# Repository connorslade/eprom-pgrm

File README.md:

# eprom-pgrm

Reader and programmer for 27 series EPROMs.

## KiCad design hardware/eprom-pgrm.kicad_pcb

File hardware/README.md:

# hardware

[View PCB / Schematic with KiCanvas](https://kicanvas.org/?repo=https%3A%2F%2Fgithub.com%2Fconnorslade%2Feprom-pgrm%2Ftree%2Fmain%2Fhardware)

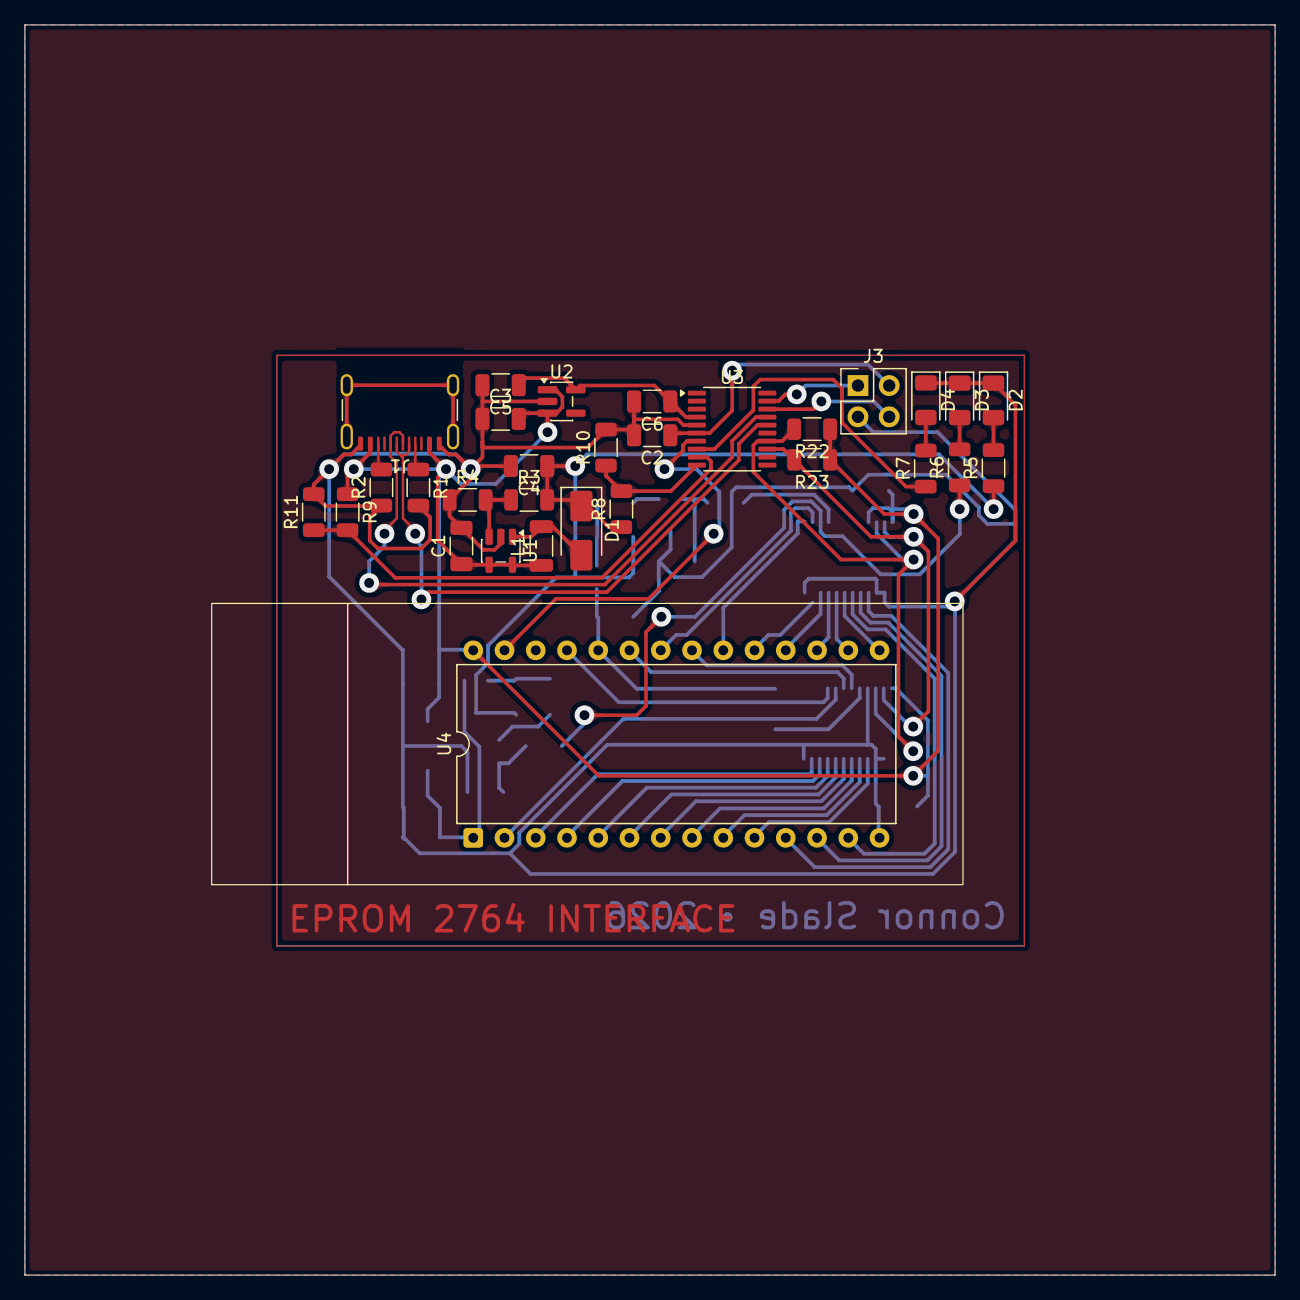
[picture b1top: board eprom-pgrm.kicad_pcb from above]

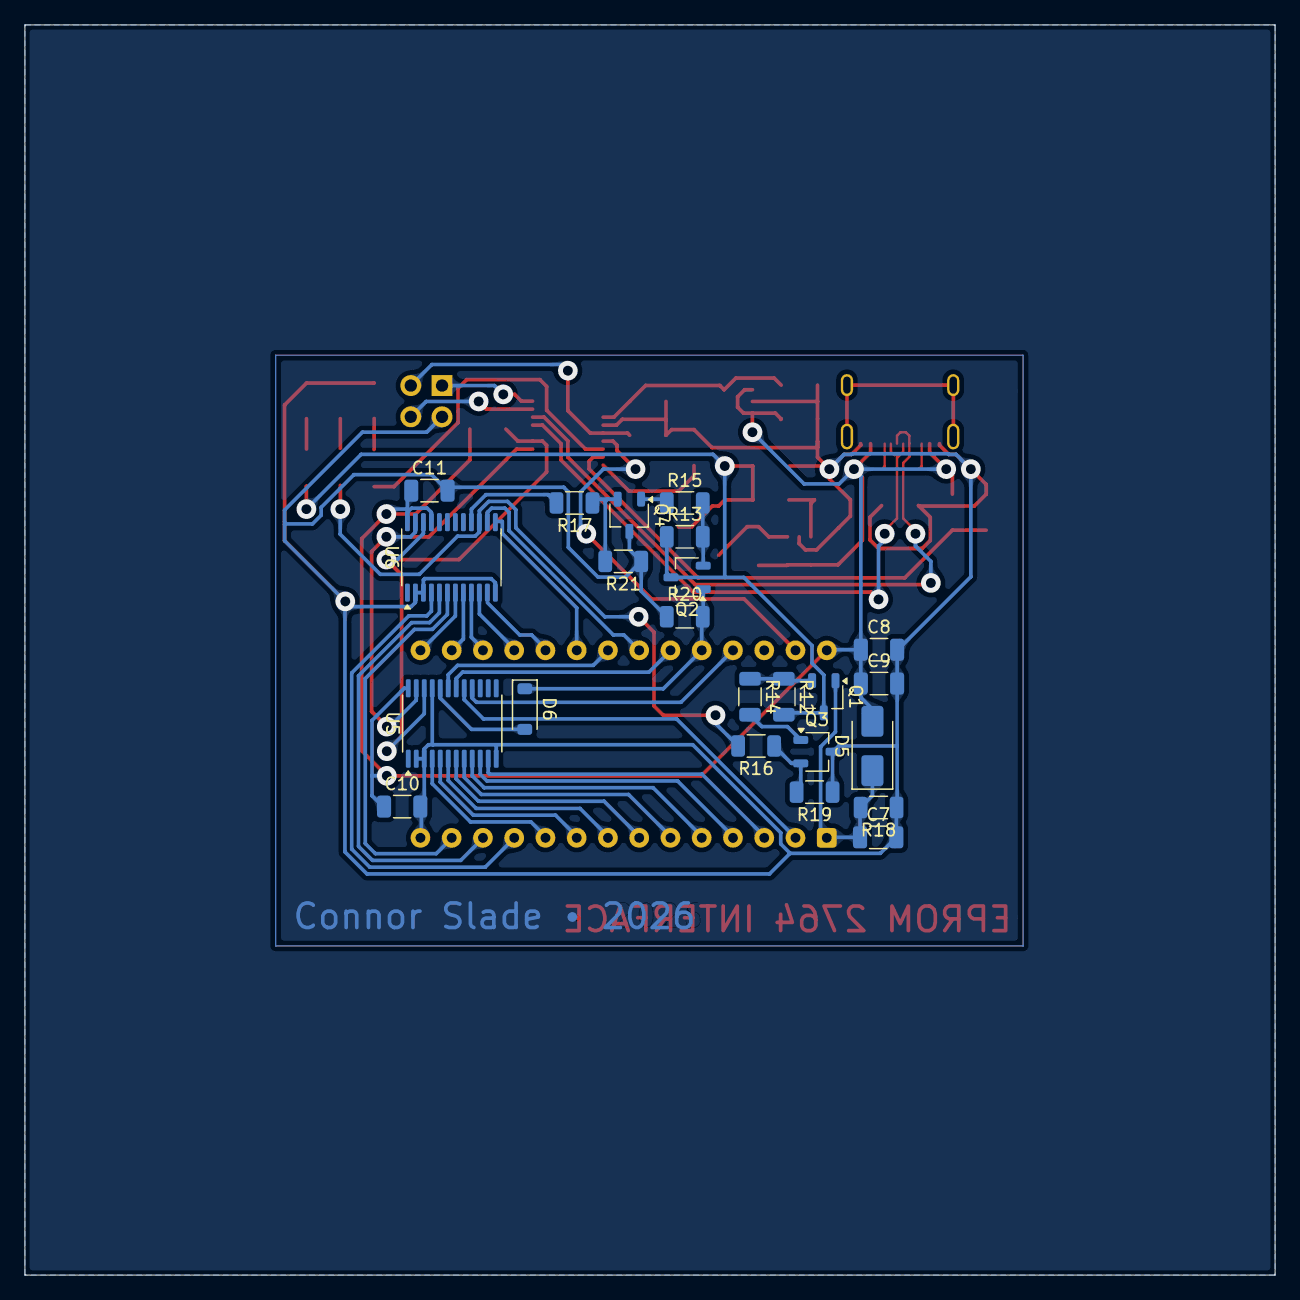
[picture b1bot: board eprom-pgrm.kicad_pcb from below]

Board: 2 copper layers, 101.6 x 101.6 mm, 53 parts (23 on the bottom side), 55 nets.

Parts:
C1, C4: 4.7μF; C_1206_3216Metric
C2: 10nF; C_1206_3216Metric
C3, C6, C7, C9, C10, C11: 100nF; C_1206_3216Metric
C5, C8: 1μF; C_1206_3216Metric
D1, D5: D_SBD; D_SMA
D2, D3, D4: LED; LED_1206_3216Metric
D6: A7; D_SOD-123
J1: USB_C_USB2.0_16P; GCT_USB4105-03-A
J3: Conn_02x02; PinHeader_2x02_P2.54mm_Vertical
L1: 10μH; L_1206_3216Metric
Q1, Q2: PNP; TSOT-23
Q3, Q4: NPN; TSOT-23
R1, R2: 5.1kΩ; R_1206_3216Metric
R3: 91kΩ; R_1206_3216Metric
R4, R12, R13, R18, R20: 10kΩ; R_1206_3216Metric
R5, R14, R15: 2kΩ; R_1206_3216Metric
R6, R7: 330Ω; R_1206_3216Metric
R8: 100kΩ; R_1206_3216Metric
R9: 39kΩ; R_1206_3216Metric
R10: 20kΩ; R_1206_3216Metric
R11: 27kΩ; R_1206_3216Metric
R16, R17, R19, R21, R22, R23: 4.7kΩ; R_1206_3216Metric
U1: AP3012; SOT-23-5
U2: TCR2EF33_LMCT; SC-74A-5_1.55x2.9mm_P0.95mm
U3: STM32C071FBPx; TSSOP-20_4.4x6.5mm_P0.65mm
U4: 2764; 28-6554-10
U5, U6: TSSOP-24_4.4x7.8mm_P0.65mm

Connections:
+3V3: C5.1, C6.1, U2.5 (VOUT), U3.4 (VDD)
+5V: C1.1, C3.2, C8.1, C9.1, C10.1, C11.1, D5.2 (A), J1.A4 (VBUS), J1.A9 (VBUS), J1.B4 (VBUS), J1.B9 (VBUS), L1.1, R9.1, R22.1, R23.1, U1.4 (~SHDN), U1.5 (IN), U2.1 (VIN), U2.3 (CONTROL), U4.28 (VCC), U5.24 (VCC), U6.21 (A0), U6.24 (VCC)
+12V: C4.1, D1.1 (K), Q1.3 (E), Q2.3 (E), R3.2, R5.1, R8.1, R12.2, R13.1
/5V_SENSE: R9.2, R11.1, U3.9 (PA2)
/12V_SENSE: R8.2, R10.1, U3.10 (PA3)
/A0: U4.10 (A0), U5.4 (IO0_0)
/A1: U4.9 (A1), U5.5 (IO0_1)
/A2: U4.8 (A2), U5.6 (IO0_2)
/A3: U4.7 (A3), U5.7 (IO0_3)
/A4: U4.6 (A4), U5.8 (IO0_4)
/A5: U4.5 (A5), U5.9 (IO0_5)
/A6: U4.4 (A6), U5.10 (IO0_6)
/A7: U4.3 (A7), U5.11 (IO0_7)
/A8: U4.25 (A8), U5.16 (IO1_3)
/A9: D6.2 (A), U5.20 (IO1_7)
/A9_SIG: D6.1 (K), Q2.1 (C), R20.2, U4.24 (A9)
/A10: U4.21 (A10), U5.19 (IO1_6)
/A11: U4.23 (A11), U5.18 (IO1_5)
/A12: U4.2 (A12), U5.17 (IO1_4)
/CE: U4.20 (~CE), U6.13 (IO1_0)
/D0: U4.11 (D0), U6.4 (IO0_0)
/D1: U4.12 (D1), U6.5 (IO0_1)
/D2: U4.13 (D2), U6.6 (IO0_2)
/D3: U4.15 (D3), U6.7 (IO0_3)
/D4: U4.16 (D4), U6.8 (IO0_4)
/D5: U4.17 (D5), U6.9 (IO0_5)
/D6: U4.18 (D6), U6.10 (IO0_6)
/D7: U4.19 (D7), U6.11 (IO0_7)
/D+: J1.A6 (D+), J1.B6 (D+), U3.17 (PA12)
/D-: J1.A7 (D-), J1.B7 (D-), U3.16 (PA11)
/IND: R7.1, U3.8 (PA1)
/NRST: C2.1, J3.2, U3.6 (PF2)
/OE: U4.22 (~OE), U6.14 (IO1_1)
/PGE: R6.1, R16.2, U6.15 (IO1_2)
/PGP: U3.7 (PA0), U4.27 (~PGM)
/SCL: R22.2, U3.14 (PA7), U5.22 (SCL), U6.22 (SCL)
/SDA: R23.2, U3.13 (PA6), U5.23 (SDA), U6.23 (SDA)
/SIG: R17.2, U6.16 (IO1_3)
/SWCLK: J3.1, U3.19 (PA14/PA15)
/SWIO: J3.4, U3.18 (PA13)
GND: C1.2, C2.2, C3.1, C4.2, C5.2, C6.2, C7.2, C8.2, C9.2, C10.2, C11.2, D2.1 (K), D3.1 (K), D4.1 (K), J1.A1 (GND), J1.A12 (GND), J1.B1 (GND), J1.B12 (GND), J3.3, Q3.3 (E), Q4.3 (E), R1.2, R2.1, R4.1, R10.2, R11.2, R18.1, R19.1, R20.1, R21.1, U1.2 (GND), U2.2 (GND), U3.5 (VSS), U4.14 (GND), U5.2 (A1), U5.3 (A2), U5.12 (GND), U5.21 (A0), U6.2 (A1), U6.3 (A2), U6.12 (GND)
unnamed: D1.2 (A), L1.2, U1.1 (SW)
unnamed: D2.2 (A), R5.2
unnamed: D3.2 (A), R6.2
unnamed: D4.2 (A), R7.2
unnamed: J1.A5 (CC1), R1.1
unnamed: J1.B5 (CC2), R2.2
unnamed: Q1.2 (B), R12.1, R14.1
unnamed: Q2.2 (B), R13.2, R15.2
unnamed: Q3.2 (B), R16.1, R19.2
unnamed: Q3.1 (C), R14.2
unnamed: Q4.2 (B), R17.1, R21.2
unnamed: Q4.1 (C), R15.1
unnamed: R3.1, R4.2, U1.3 (FB)
VPP: C7.1, D5.1 (K), Q1.1 (C), R18.2, U4.1 (VPP)
